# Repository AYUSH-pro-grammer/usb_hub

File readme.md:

# USB 2.0 4-Port Hub

Custom USB hub design that uses the FE1.1s USB hub controller. Includes one USB-C port to connect the host computer and four USB-A ports to connect different USB devices.

This project provides you with the PCB design, circuit diagram, 3D enclosure design, and gerber files. This enclosure should be 3D printed in PLA filament, and it will have a wooden look.

## Why This Project?

In this project, a compact and custom USB hub design is planned which will expand one USB-C port to four USB-A ports.

Unlike a USB hub available for purchase off the shelf, this particular project involves designing an entire USB hub from scratch. It allows us practical experience with the design of a USB hub, integration with a USB hub controller, circuit design, and enclosure modeling using 3D printing.

The custom enclosure is planned for 3D printing from PLA with wooden look design.

## Project Images

### 3D PCB Design

**Front View**

**Back View**

### Enclosure Design

**Case Open**

**Case Clos**

### PCB Layout and Routing

**PCB Routing**

### Circuit Schematic

## Bill of Materials (BOM)

| Component Name | Quantity | Price (USD) | Purchase Link |
|---|---:|---:|---|
| FE1.1s USB 2.0 4-Port Hub Controller | 1 | $0.72 | [Buy](https://www.lcsc.com/product-detail/C42383361.html) |
| 12MHz Crystal Oscillator | 1 | $0.10 | [Buy](https://www.lcsc.com/product-detail/C518158.html) |
| USB-C Receptacle Connector 16-Pin | 1 | $0.17 | [Buy](https://www.lcsc.com/product-detail/C165948.html) |
| USB-A Female Receptacle Connector | 4 | $3.05 | [Buy](https://www.lcsc.com/product-detail/C5355659.html) |
| 3-Pin 2.54mm Pin Header | 2 | $0.64 | [Buy](https://www.lcsc.com/product-detail/C265013.html) |
| 2A Resettable PTC Fuse | 1 | $0.18 | [Buy](https://www.lcsc.com/product-detail/C315901.html) |
| 100µF 6.3V Ceramic Capacitor | 4 | $1.58 | [Buy](https://www.lcsc.com/product-detail/C141660.html) |
| 10µF 16V Ceramic Capacitor | 2 | $0.20 | [Buy](https://www.lcsc.com/product-detail/C307561.html) |
| 1µF 50V Ceramic Capacitor | 1 | $0.04 | [Buy](https://www.lcsc.com/product-detail/C28323.html) |
| 2.7kΩ Resistor | 1 | $0.002 | [Buy](https://www.lcsc.com/product-detail/C25994.html) |
| 5.1kΩ Resistor | 2 | $0.003 | [Buy](https://www.lcsc.com/product-detail/C23186.html) |
| 1kΩ Resistor | 3 | $0.005 | [Buy](https://www.lcsc.com/product-detail/C21190.html) |
| Green LED 0603 | 4 | $0.33 | [Buy](https://www.lcsc.com/product-detail/C2994781.html) |
| Red LED 0603 | 1 | $0.008 | [Buy](https://www.lcsc.com/product-detail/C2286.html) |
| 1mm Screws | 4 | $0.40 | [Buy](https://store.rc4wd.com/1mm-x-6mm-Machine-Screw-and-Nut_p_3392.html?srsltid=AYCX9vIycEosIwabGsPoTfw73K-fBxiC5gdlN2avYkQrfX3chnO0lzBLuHc) |
| PCB Fabrication | 1 | $4.00 | [JLCPCB](https://jlcpcb.com) |
| Shipping | 1 | $8.00 | — |

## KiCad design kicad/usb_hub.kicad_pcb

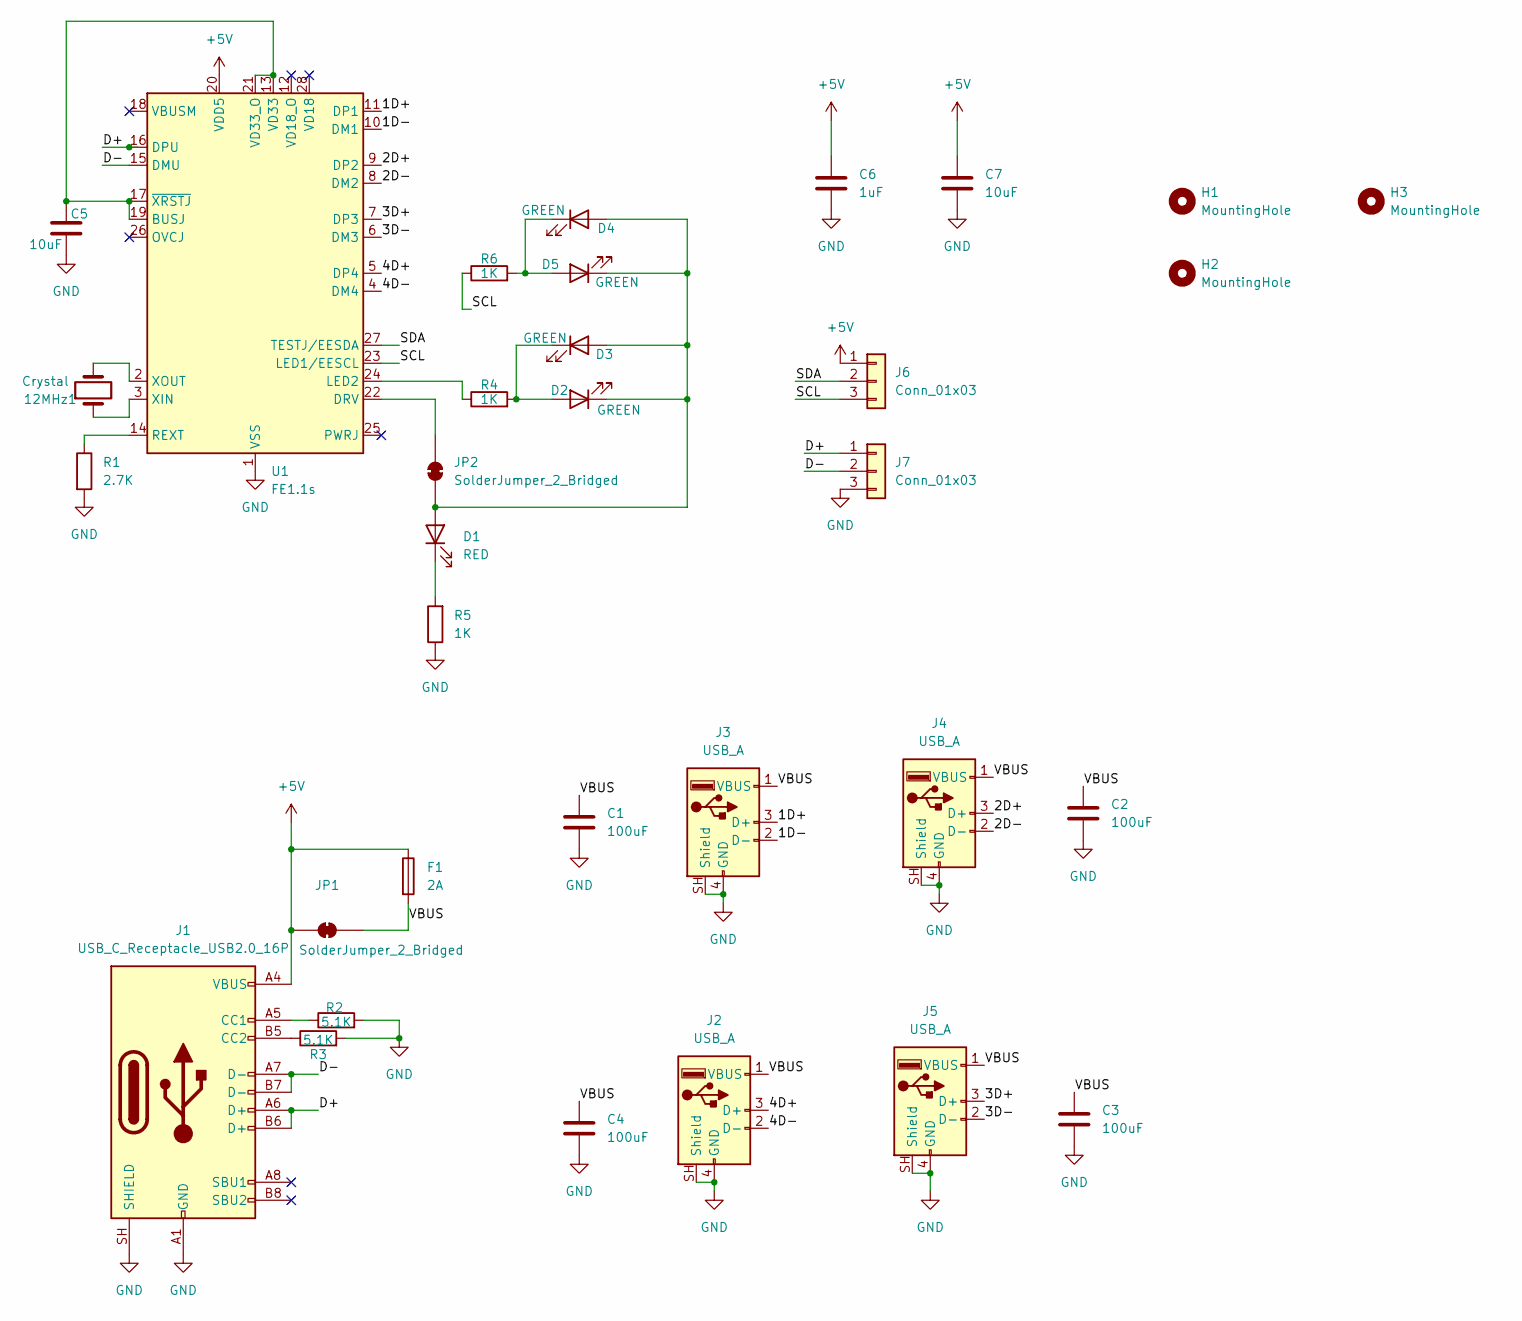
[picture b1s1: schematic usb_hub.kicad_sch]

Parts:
12MHz1: Crystal; Crystal_SMD_3225-4Pin_3.2x2.5mm
C1, C2, C3, C4: 100uF; C_0805_2012Metric
C5, C7: 10uF; C_0805_2012Metric
C6: 1uF; C_0805_2012Metric
D1: RED; LED_0603_1608Metric
D2, D3, D4, D5: GREEN; LED_0603_1608Metric
F1: 2A; Fuse_1812_4532Metric
H1, H2, H3: MountingHole; Mounting_Wuerth_WA-SMSI-M1.6_H3mm_ThreadDepth1.8mm_97730306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
J1: USB_C_Receptacle_USB2.0_16P; USB_C_Receptacle_HRO_TYPE-C-31-M-12
J2, J3, J4, J5: USB_A; USB_A_Receptacle_GCT_USB1046
J6, J7: Conn_01x03; PinHeader_1x03_P2.54mm_Vertical
JP1, JP2: SolderJumper_2_Bridged; SolderJumper-2_P1.3mm_Open_RoundedPad1.0x1.5mm
R1: 2.7K; R_0603_1608Metric
R2, R3: 5.1K; R_0603_1608Metric
R4, R5, R6: 1K; R_0603_1608Metric
U1: FE1.1s; SSOP-28_3.9x9.9mm_P0.635mm

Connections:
+5V: C6.1, C7.1, F1.1, J1.A4 (VBUS), J1.A9 (VBUS), J1.B4 (VBUS), J1.B9 (VBUS), J6.1, JP1.1 (A), U1.20 (VDD5)
/1D+: J3.3 (D+), U1.11 (DP1)
/1D-: J3.2 (D-), U1.10 (DM1)
/2D+: J4.3 (D+), U1.9 (DP2)
/2D-: J4.2 (D-), U1.8 (DM2)
/3D+: J5.3 (D+), U1.7 (DP3)
/3D-: J5.2 (D-), U1.6 (DM3)
/4D+: J2.3 (D+), U1.5 (DP4)
/4D-: J2.2 (D-), U1.4 (DM4)
/D+: J1.A6 (D+), J1.B6 (D+), J7.1, U1.16 (DPU)
/D-: J1.A7 (D-), J1.B7 (D-), J7.2, U1.15 (DMU)
/SCL: J6.3, R6.1, U1.23 (LED1/EESCL)
/SDA: J6.2, U1.27 (TESTJ/EESDA)
/VBUS: C1.1, C2.1, C3.1, C4.1, F1.2, J2.1 (VBUS), J3.1 (VBUS), J4.1 (VBUS), J5.1 (VBUS), JP1.2 (B)
GND: C1.2, C2.2, C3.2, C4.2, C5.2, C6.2, C7.2, J1.A1 (GND), J1.A12 (GND), J1.B1 (GND), J1.B12 (GND), J1.SH (SHIELD), J2.4 (GND), J2.SH (Shield), J3.4 (GND), J3.SH (Shield), J4.4 (GND), J4.SH (Shield), J5.4 (GND), J5.SH (Shield), J7.3, R1.2, R2.2, R3.2, R5.1, U1.1 (VSS)
unnamed: D1.2 (A), D2.1 (K), D3.2 (A), D4.2 (A), D5.1 (K), JP2.1 (A)
unnamed: D1.1 (K), R5.2
unnamed: D2.2 (A), D3.1 (K), R4.2
unnamed: D4.1 (K), D5.2 (A), R6.2
unnamed: J1.A5 (CC1), R2.1
unnamed: J1.B5 (CC2), R3.1
unnamed: JP2.2 (B), U1.22 (DRV)
unnamed: C5.1, U1.13 (VD33), U1.17 (~XRSTJ), U1.19 (BUSJ), U1.21 (VD33_O)
unnamed: R4.1, U1.24 (LED2)
unnamed: R1.1, U1.14 (REXT)
unnamed: 12MHz1.1, U1.3 (XIN)
unnamed: 12MHz1.2, U1.2 (XOUT)

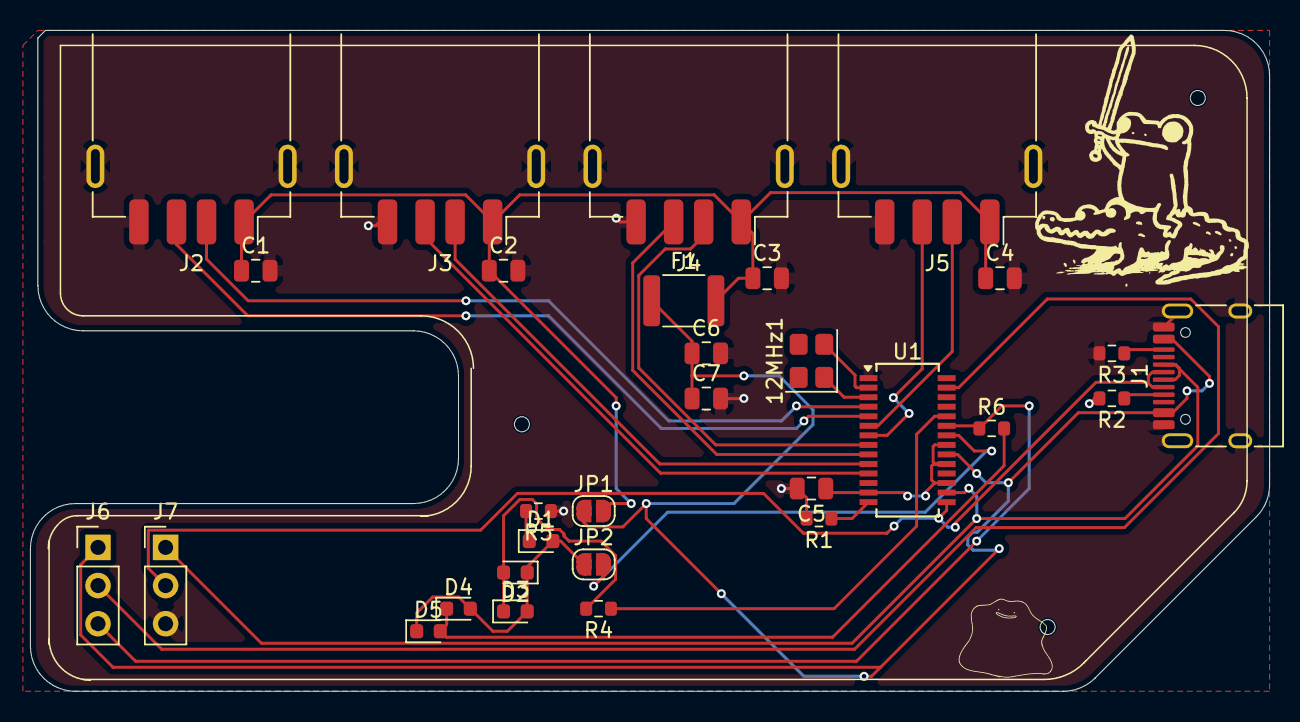
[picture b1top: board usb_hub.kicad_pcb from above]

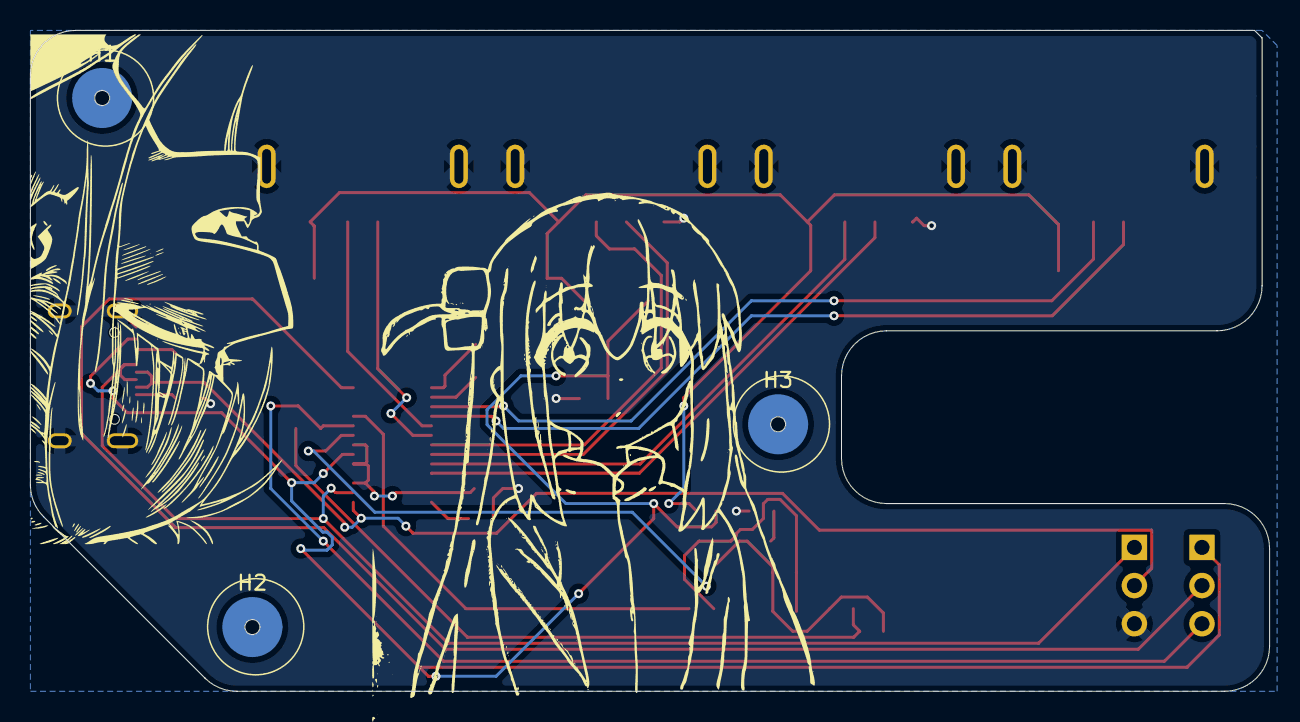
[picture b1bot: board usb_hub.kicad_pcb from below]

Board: 2 copper layers, 82.5 x 44.0 mm, 33 parts (3 on the bottom side), 27 nets.

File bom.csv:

Name,Designator,Quantity,Footprint,LCSC Part Number,Unit Price (USD),Total Price (USD),URL
"FE1.1s USB 2.0 4-Port Hub Controller (SSOP-28)",U1,1,SSOP-28,C42383361,0.7158,0.72,https://www.lcsc.com/product-detail/C42383361.html
"12MHz Crystal Oscillator (SMD 3225 4P)",12MHz1,1,SMD 3225,C518158,0.0981,0.10,https://www.lcsc.com/product-detail/C518158.html
"USB-C Receptacle Connector 16-Pin (TYPE-C-31-M-12)",J1,1,HRO TYPE-C-31-M-12,C165948,0.1739,0.17,https://www.lcsc.com/product-detail/C165948.html
"USB-A Female Receptacle Connector (USB1040-GF-L-B)","J2, J3, J4, J5",4,GCT USB1046,C5355659,0.7632,3.05,https://www.lcsc.com/product-detail/C5355659.html
"Pin Header 3 Position 2.54mm Pitch Single Row","J6, J7",2,2.54mm 1x03,C265013,0.3214,0.64,https://www.lcsc.com/product-detail/C265013.html
"Polymeric PTC Resettable Fuse 2A 12V 1812",F1,1,1812,C315901,0.1769,0.18,https://www.lcsc.com/product-detail/C315901.html
"100uF 6.3V Ceramic Capacitor X5R 0805","C1, C2, C3, C4",4,0805,C141660,0.3949,1.58,https://www.lcsc.com/product-detail/C141660.html
"10uF 16V Ceramic Capacitor X6S 0805","C5, C7",2,0805,C307561,0.0996,0.20,https://www.lcsc.com/product-detail/C307561.html
"1uF 50V Ceramic Capacitor X7R 0805",C6,1,0805,C28323,0.0426,0.04,https://www.lcsc.com/product-detail/C28323.html
"2.7kΩ 100mW 0603 Resistor",R1,1,0603,C25994,0.0020,0.002,https://www.lcsc.com/product-detail/C25994.html
"5.1kΩ 100mW 0603 Resistor","R2, R3",2,0603,C23186,0.0016,0.003,https://www.lcsc.com/product-detail/C23186.html
"1kΩ 100mW 0603 Resistor","R4, R5, R6",3,0603,C21190,0.0017,0.005,https://www.lcsc.com/product-detail/C21190.html
"Green 525nm LED Indication 0603","D2, D3, D4, D5",4,0603,C2994781,0.0821,0.33,https://www.lcsc.com/product-detail/C2994781.html
"Red 645nm LED Indication 0603",D1,1,0603,C2286,0.0077,0.008,https://www.lcsc.com/product-detail/C2286.html
PCB Fabrication,,1,,,4.00,4.00,https://www.jlcpcb.com
Shipping,,1,,,8.00,8.00,
GRAND TOTAL,,,,,,19.03,
